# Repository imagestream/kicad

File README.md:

# kicad
Kicad designs and libraries

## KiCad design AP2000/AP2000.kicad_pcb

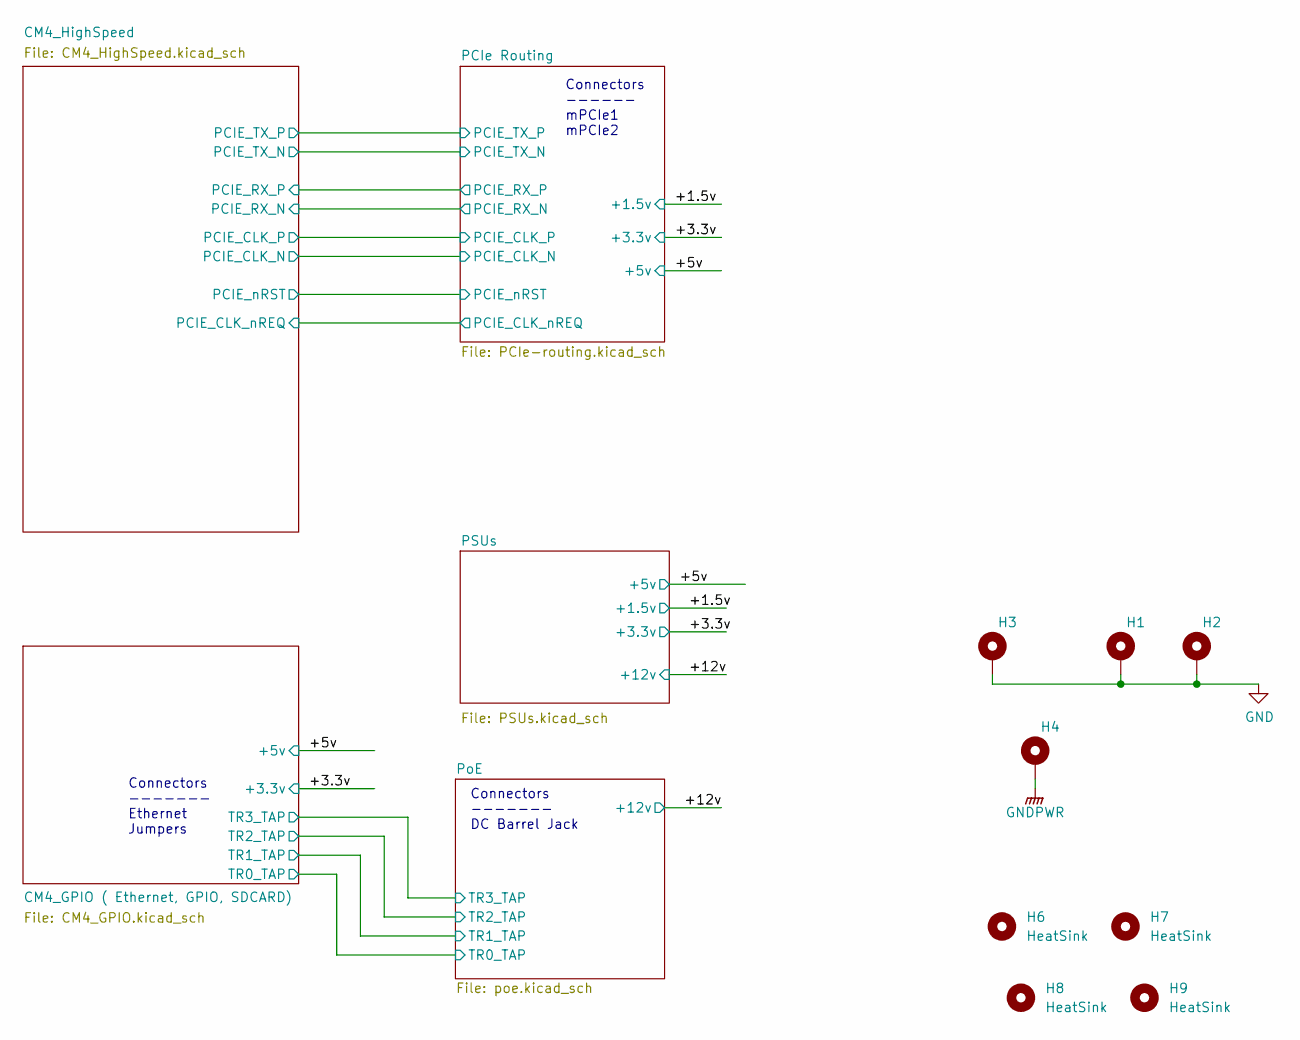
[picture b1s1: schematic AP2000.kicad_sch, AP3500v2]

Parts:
H1: HeatSink; MountingHole_3.7mm_Pad_TopBottom
H2, H3, H4: Mounting Hole; MountingHole_3.7mm_Pad_TopBottom
H6, H7, H8, H9: HeatSink; CM4_Mounting_Hole

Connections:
GND: H1.1, H2.1, H3.1; also elsewhere on the board
GNDPWR: H4.1; also elsewhere on the board

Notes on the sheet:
Connectors ------- Ethernet Jumpers
Connectors ------- DC Barrel Jack
Connectors ------ mPCIe1 mPCIe2

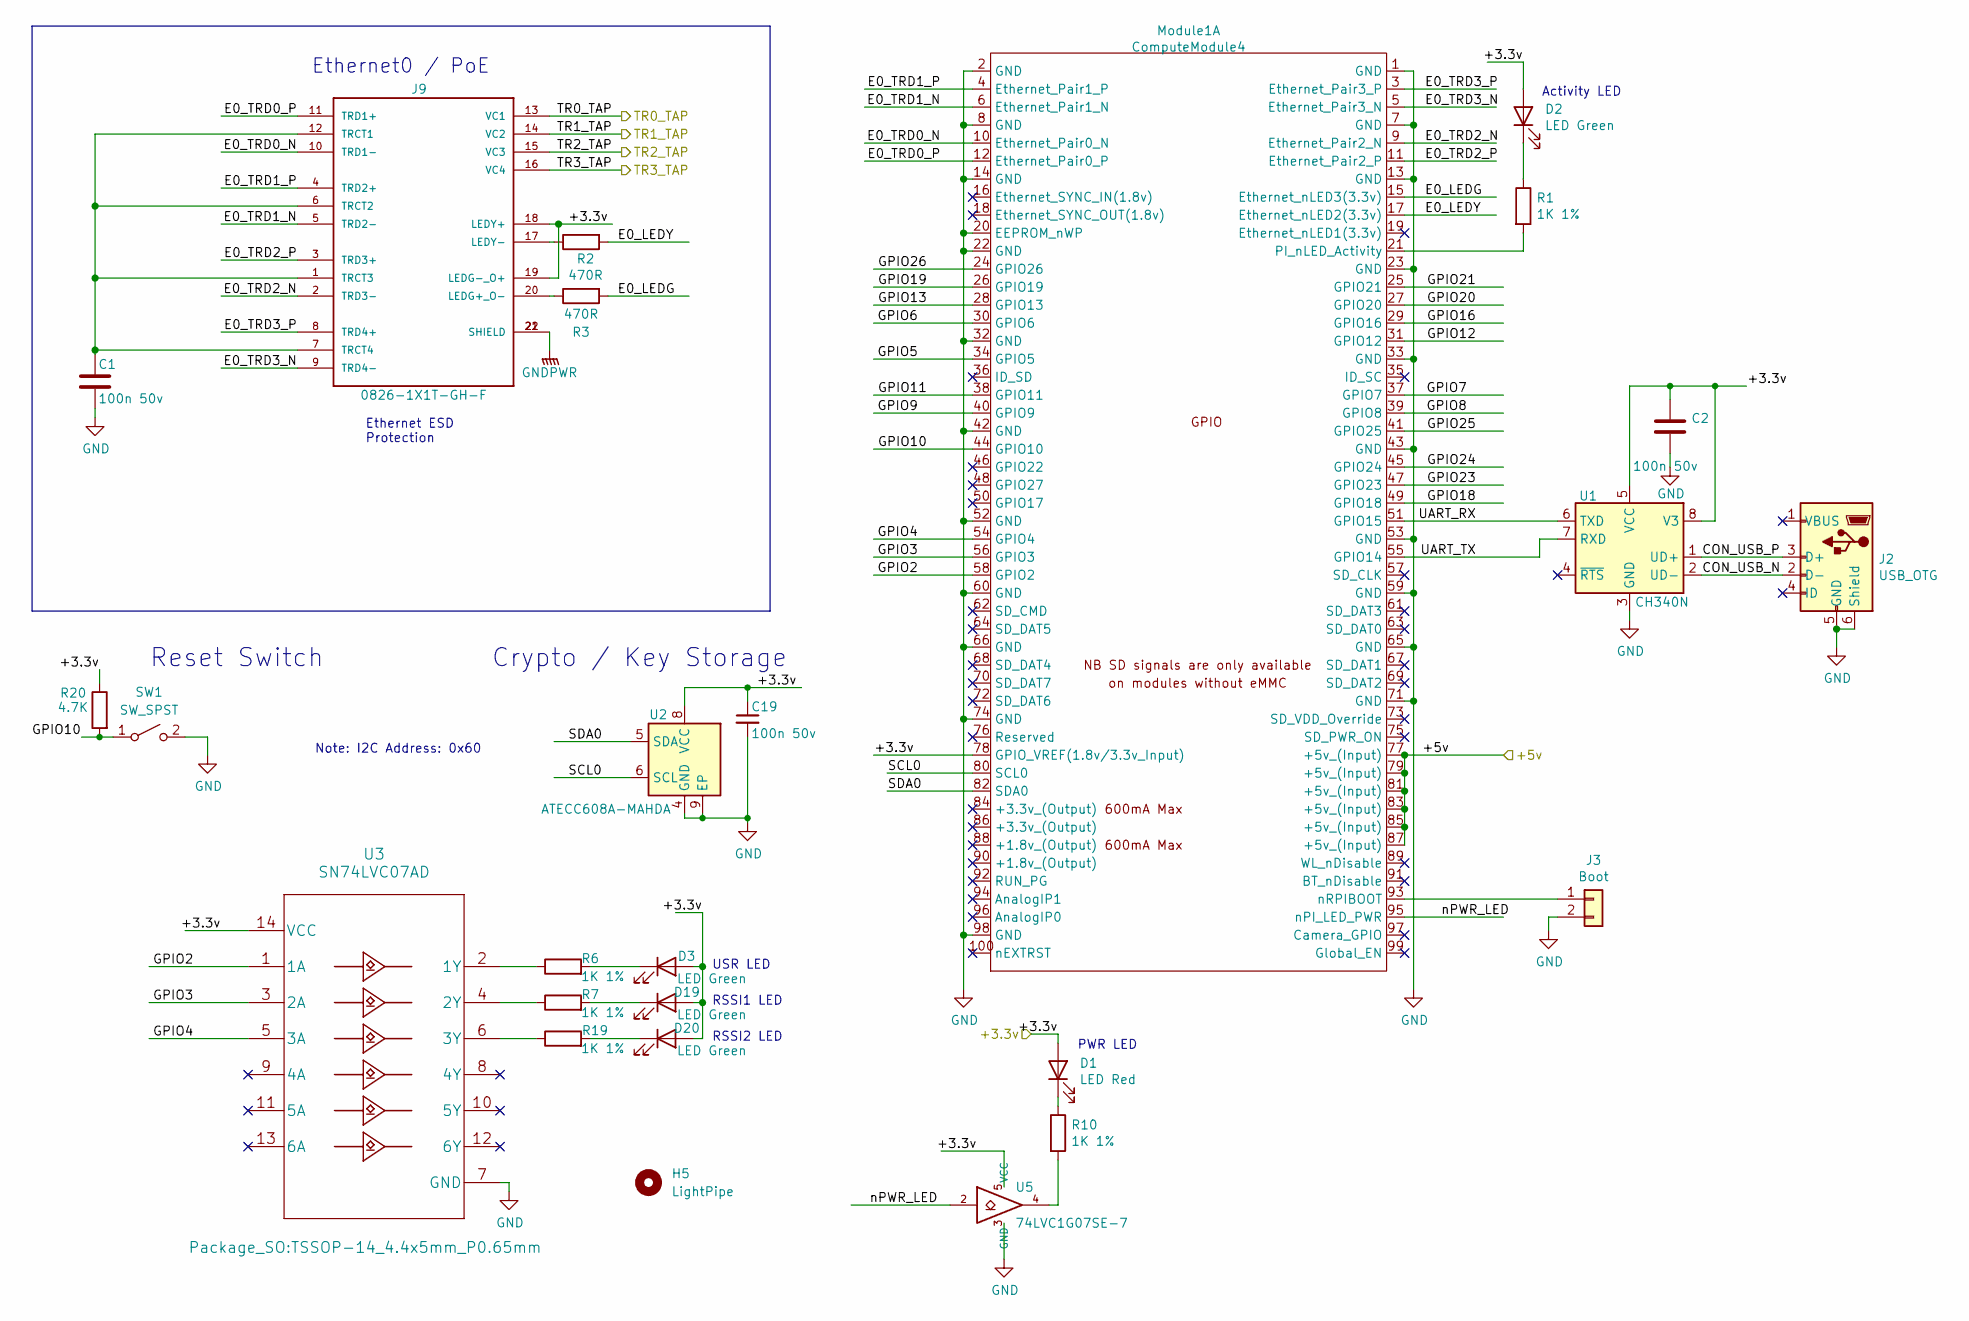
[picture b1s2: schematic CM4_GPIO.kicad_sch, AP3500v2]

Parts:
C1, C2: 100n 50v; C_0603_1608Metric; Part Description 100nF 10% or 20% 50V Ceramic Capacitor 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; LCSC C14663
C19: 100n 50v; C_0603_1608Metric; PartsBoxID 0603-100nF-X7R-50V; LCSC C14663
D1: LED Red; LED_0603_1608Metric; Part Description Red 620nm LED Indication - Discrete 2.2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; LCSC C2286
D2, D3, D19, D20: LED Green; LED_0603_1608Metric; Part Description Green 572nm LED Indication - Discrete 2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; LCSC C72043
H5: LightPipe; VCC_LightPipe_7511A62
J2: USB_OTG; AMPHENOL_10118194-0001LF; Part Description USB - micro B USB 2.0 Receptacle Connec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; LCSC C132563
J3: Boot; PinHeader_1x02_P2.54mm_Vertical; Part Description PinHeader_2x07_P2.54mm_Vertical
J9: 0826-1X1T-GH-F; BEL_0826-1X1T-GH-F; PartsBoxID 0826-1X1T-GH-F
Module1: ComputeModule4; Raspberry-Pi-4-Compute-Module; Part Description 100 Position Connector Receptacle, Cent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
R1, R6, R7, R10, R19: 1K 1%; R_0603_1608Metric; Part Description Resistor 1K M1005 1% 63mW; LCSC C21190
R2, R3: 470R; R_0603_1608Metric; Part Description Resistor 470R M1005 1% 63mW; LCSC C23179
R20: 4.7K; R_0603_1608Metric; PartsBoxID 0603-4.7K-1%; LCSC C23162
SW1: SW_SPST; SWITCH TACTILE SPST-NO 0.05A 12V; PartsBox PTS645VK582LFS
U1: CH340N; SOP-8_5.28x5.23mm_P1.27mm
U2: ATECC608A-MAHDA; DFN-8-1EP_3x2mm_P0.5mm_EP1.3x1.5mm; PartsBoxID ATECC608A-MAHDA-T
U3: SN74LVC07AD; TSSOP-14_4.4x5mm_P0.65mm; PartsBoxID SN74LVC07AD; LCSC C7809
U5: 74LVC1G07SE-7; SOT-23-5; Part Description Buffer, Non-Inverting 1 Element 1 Bit p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; LCSC C7829

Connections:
/+3.3v: C2.1, C19.1, D1.2 (A), D2.2 (A), D3.2 (A), D19.2 (A), D20.2 (A), J9.18 (LEDY+), J9.19 (LEDG-_O+), Module1.78 (GPIO_VREF(1.8v/3.3v_Input)), R20.1, U1.5 (VCC), U1.8 (V3), U2.8 (VCC), U3.14 (VCC), U5.5 (VCC); also elsewhere on the board
/+5v: Module1.77 (+5v_(Input)), Module1.79 (+5v_(Input)), Module1.81 (+5v_(Input)), Module1.83 (+5v_(Input)), Module1.85 (+5v_(Input)), Module1.87 (+5v_(Input)); also elsewhere on the board
/CM4_GPIO ( Ethernet, GPIO, SDCARD)/CON_USB_N: J2.2 (D-), U1.2 (UD-)
/CM4_GPIO ( Ethernet, GPIO, SDCARD)/CON_USB_P: J2.3 (D+), U1.1 (UD+)
/CM4_GPIO ( Ethernet, GPIO, SDCARD)/E0_LEDG: Module1.15 (Ethernet_nLED3(3.3v)), R3.2
/CM4_GPIO ( Ethernet, GPIO, SDCARD)/E0_LEDY: Module1.17 (Ethernet_nLED2(3.3v)), R2.2
/CM4_GPIO ( Ethernet, GPIO, SDCARD)/E0_TRD0_N: J9.10 (TRD1-), Module1.10 (Ethernet_Pair0_N)
/CM4_GPIO ( Ethernet, GPIO, SDCARD)/E0_TRD0_P: J9.11 (TRD1+), Module1.12 (Ethernet_Pair0_P)
/CM4_GPIO ( Ethernet, GPIO, SDCARD)/E0_TRD1_N: J9.5 (TRD2-), Module1.6 (Ethernet_Pair1_N)
/CM4_GPIO ( Ethernet, GPIO, SDCARD)/E0_TRD1_P: J9.4 (TRD2+), Module1.4 (Ethernet_Pair1_P)
/CM4_GPIO ( Ethernet, GPIO, SDCARD)/E0_TRD2_N: J9.2 (TRD3-), Module1.9 (Ethernet_Pair2_N)
/CM4_GPIO ( Ethernet, GPIO, SDCARD)/E0_TRD2_P: J9.3 (TRD3+), Module1.11 (Ethernet_Pair2_P)
/CM4_GPIO ( Ethernet, GPIO, SDCARD)/E0_TRD3_N: J9.9 (TRD4-), Module1.5 (Ethernet_Pair3_N)
/CM4_GPIO ( Ethernet, GPIO, SDCARD)/E0_TRD3_P: J9.8 (TRD4+), Module1.3 (Ethernet_Pair3_P)
/CM4_GPIO ( Ethernet, GPIO, SDCARD)/GPIO2: Module1.58 (GPIO2), U3.1 (1A)
/CM4_GPIO ( Ethernet, GPIO, SDCARD)/GPIO3: Module1.56 (GPIO3), U3.3 (2A)
/CM4_GPIO ( Ethernet, GPIO, SDCARD)/GPIO4: Module1.54 (GPIO4), U3.5 (3A)
/CM4_GPIO ( Ethernet, GPIO, SDCARD)/GPIO5: Module1.34 (GPIO5)
/CM4_GPIO ( Ethernet, GPIO, SDCARD)/GPIO6: Module1.30 (GPIO6)
/CM4_GPIO ( Ethernet, GPIO, SDCARD)/GPIO7: Module1.37 (GPIO7)
/CM4_GPIO ( Ethernet, GPIO, SDCARD)/GPIO8: Module1.39 (GPIO8)
/CM4_GPIO ( Ethernet, GPIO, SDCARD)/GPIO9: Module1.40 (GPIO9)
/CM4_GPIO ( Ethernet, GPIO, SDCARD)/GPIO10: Module1.44 (GPIO10), R20.2, SW1.1 (A)
/CM4_GPIO ( Ethernet, GPIO, SDCARD)/GPIO11: Module1.38 (GPIO11)
/CM4_GPIO ( Ethernet, GPIO, SDCARD)/GPIO12: Module1.31 (GPIO12)
/CM4_GPIO ( Ethernet, GPIO, SDCARD)/GPIO13: Module1.28 (GPIO13)
/CM4_GPIO ( Ethernet, GPIO, SDCARD)/GPIO16: Module1.29 (GPIO16)
/CM4_GPIO ( Ethernet, GPIO, SDCARD)/GPIO18: Module1.49 (GPIO18)
/CM4_GPIO ( Ethernet, GPIO, SDCARD)/GPIO19: Module1.26 (GPIO19)
/CM4_GPIO ( Ethernet, GPIO, SDCARD)/GPIO20: Module1.27 (GPIO20)
/CM4_GPIO ( Ethernet, GPIO, SDCARD)/GPIO21: Module1.25 (GPIO21)
/CM4_GPIO ( Ethernet, GPIO, SDCARD)/GPIO23: Module1.47 (GPIO23)
/CM4_GPIO ( Ethernet, GPIO, SDCARD)/GPIO24: Module1.45 (GPIO24)
/CM4_GPIO ( Ethernet, GPIO, SDCARD)/GPIO25: Module1.41 (GPIO25)
/CM4_GPIO ( Ethernet, GPIO, SDCARD)/GPIO26: Module1.24 (GPIO26)
/CM4_GPIO ( Ethernet, GPIO, SDCARD)/SCL0: Module1.80 (SCL0), U2.6 (SCL)
/CM4_GPIO ( Ethernet, GPIO, SDCARD)/SDA0: Module1.82 (SDA0), U2.5 (SDA)
/CM4_GPIO ( Ethernet, GPIO, SDCARD)/TR0_TAP: J9.13 (VC1); also elsewhere on the board
/CM4_GPIO ( Ethernet, GPIO, SDCARD)/TR1_TAP: J9.14 (VC2); also elsewhere on the board
/CM4_GPIO ( Ethernet, GPIO, SDCARD)/TR2_TAP: J9.15 (VC3); also elsewhere on the board
/CM4_GPIO ( Ethernet, GPIO, SDCARD)/TR3_TAP: J9.16 (VC4); also elsewhere on the board
/CM4_GPIO ( Ethernet, GPIO, SDCARD)/UART_RX: Module1.51 (GPIO15), U1.6 (TXD)
/CM4_GPIO ( Ethernet, GPIO, SDCARD)/UART_TX: Module1.55 (GPIO14), U1.7 (RXD)
/CM4_GPIO ( Ethernet, GPIO, SDCARD)/nPWR_LED: Module1.95 (nPI_LED_PWR), U5.2
GND: C1.2, C2.2, C19.2, J2.5 (GND), J2.6 (Shield), J3.2, Module1.1 (GND), Module1.2 (GND), Module1.7 (GND), Module1.8 (GND), Module1.13 (GND), Module1.14 (GND), Module1.20 (EEPROM_nWP), Module1.22 (GND), Module1.23 (GND), Module1.32 (GND), Module1.33 (GND), Module1.42 (GND), Module1.43 (GND), Module1.52 (GND), Module1.53 (GND), Module1.59 (GND), Module1.60 (GND), Module1.65 (GND), Module1.66 (GND), Module1.71 (GND), Module1.74 (GND), Module1.98 (GND), SW1.2 (B), U1.3 (GND), U2.4 (GND), U2.9 (EP), U3.7 (GND), U5.3 (GND); also elsewhere on the board
GNDPWR: J9.21 (SHIELD), J9.22 (SHIELD); also elsewhere on the board
unnamed: C1.1, J9.1 (TRCT3), J9.6 (TRCT2), J9.7 (TRCT4), J9.12 (TRCT1)
unnamed: D1.1 (K), R10.1
unnamed: D2.1 (K), R1.1
unnamed: D3.1 (K), R6.2
unnamed: D19.1 (K), R7.2
unnamed: D20.1 (K), R19.2
unnamed: J3.1, Module1.93 (nRPIBOOT)
unnamed: J9.17 (LEDY-), R2.1
unnamed: J9.20 (LEDG+_O-), R3.1
unnamed: Module1.21 (PI_nLED_Activity), R1.2
unnamed: R6.1, U3.2 (1Y)
unnamed: R7.1, U3.4 (2Y)
unnamed: R10.2, U5.4
unnamed: R19.1, U3.6 (3Y)

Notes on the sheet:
Ethernet0 / PoE
Reset Switch
Ethernet ESD Protection
Note: I2C Address: 0x60
USR LED
RSSI1 LED
RSSI2 LED
Crypto / Key Storage
PWR LED
Activity LED

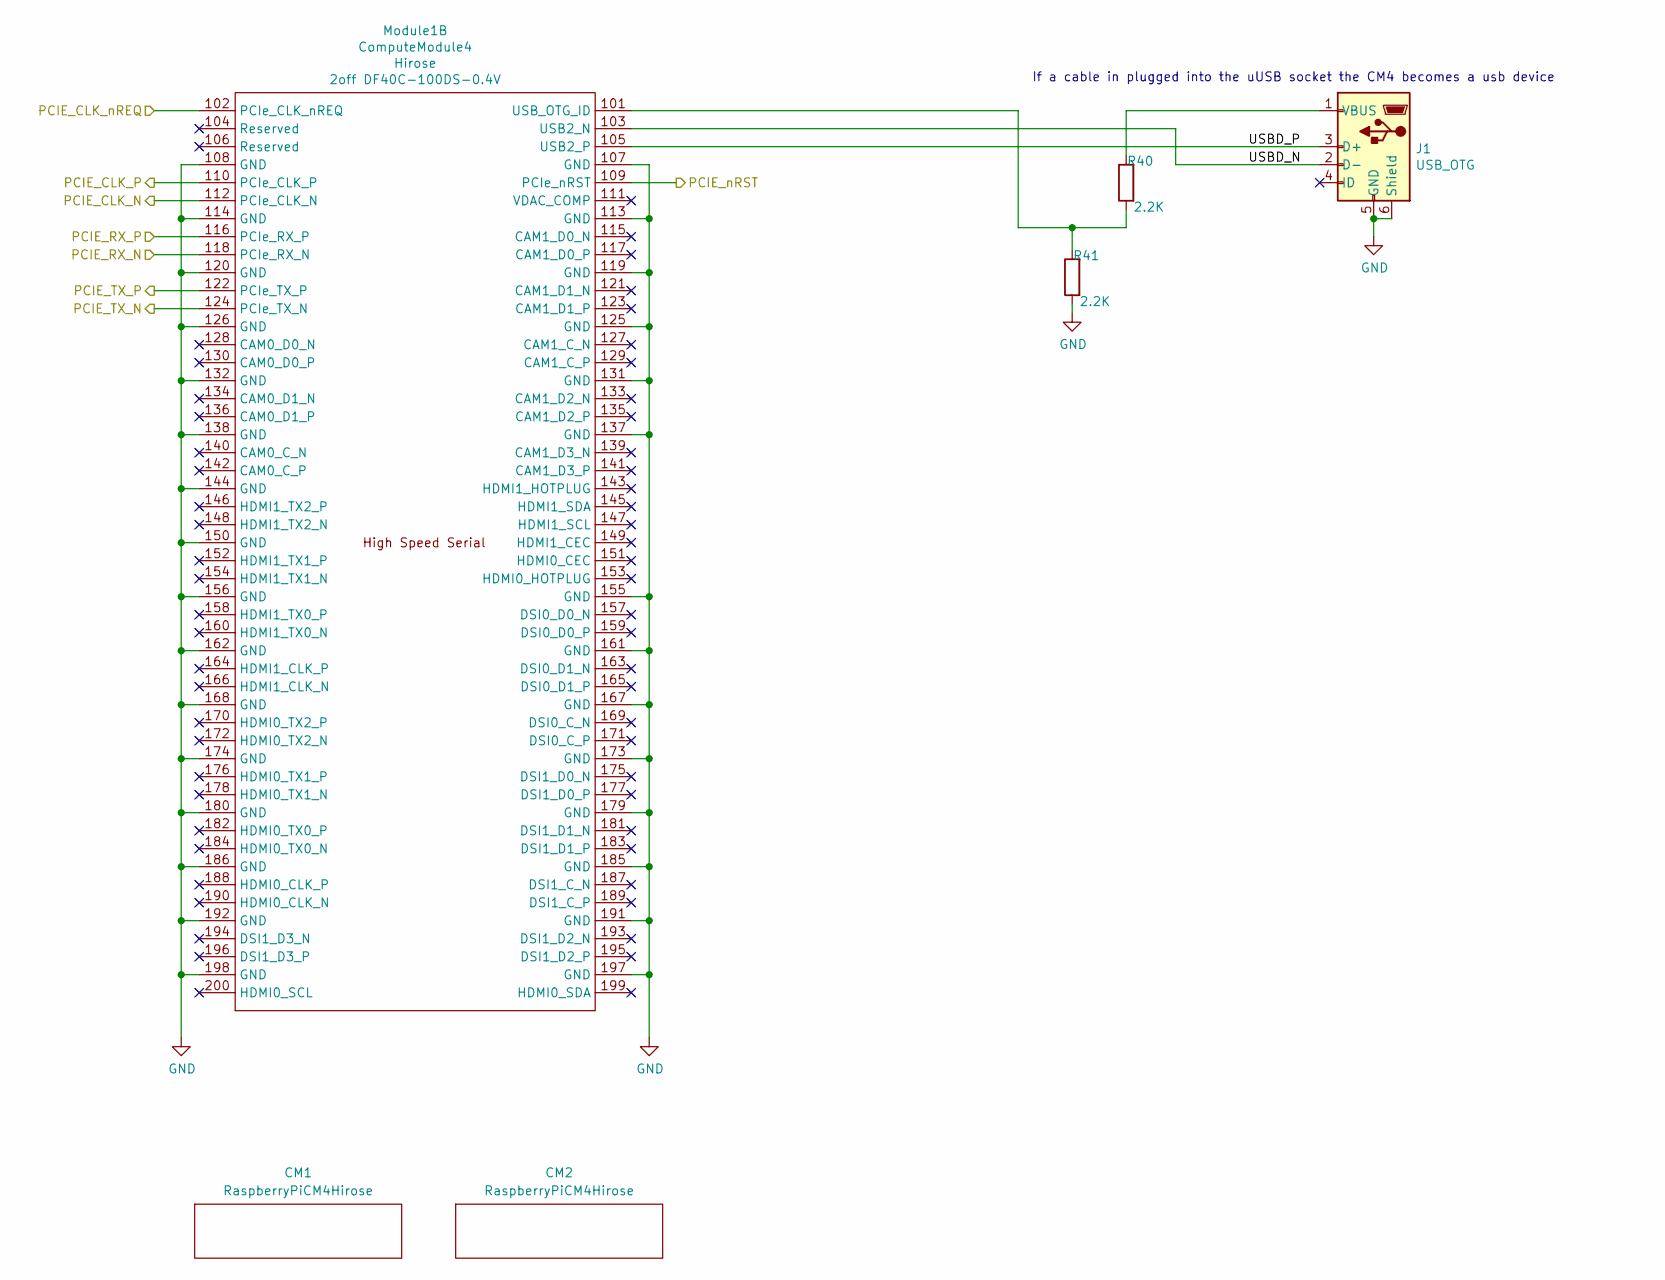
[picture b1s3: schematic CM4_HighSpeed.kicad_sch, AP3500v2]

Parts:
CM1, CM2: RaspberryPiCM4Hirose; Hirose-DF40C-100DS-0.4V; LCSC C424649
J1: USB_OTG; AMPHENOL_10118194-0001LF; Part Description USB - micro B USB 2.0 Receptacle Connec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; LCSC C132563
Module1: ComputeModule4; Raspberry-Pi-4-Compute-Module; Part Description 100 Position Connector Receptacle, Cent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
R40, R41: 2.2K; R_0603_1608Metric; PartsBoxID 0603-2.2K-1%; LCSC C4190

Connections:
/CM4_HighSpeed/PCIE_CLK_N: Module1.112 (PCIe_CLK_N); also elsewhere on the board
/CM4_HighSpeed/PCIE_CLK_P: Module1.110 (PCIe_CLK_P); also elsewhere on the board
/CM4_HighSpeed/PCIE_CLK_nREQ: Module1.102 (PCIe_CLK_nREQ); also elsewhere on the board
/CM4_HighSpeed/PCIE_RX_N: Module1.118 (PCIe_RX_N); also elsewhere on the board
/CM4_HighSpeed/PCIE_RX_P: Module1.116 (PCIe_RX_P); also elsewhere on the board
/CM4_HighSpeed/PCIE_TX_N: Module1.124 (PCIe_TX_N); also elsewhere on the board
/CM4_HighSpeed/PCIE_TX_P: Module1.122 (PCIe_TX_P); also elsewhere on the board
/CM4_HighSpeed/PCIE_nRST: Module1.109 (PCIe_nRST); also elsewhere on the board
/CM4_HighSpeed/USBD_N: J1.2 (D-), Module1.103 (USB2_N)
/CM4_HighSpeed/USBD_P: J1.3 (D+), Module1.105 (USB2_P)
GND: J1.5 (GND), J1.6 (Shield), Module1.107 (GND), Module1.108 (GND), Module1.113 (GND), Module1.114 (GND), Module1.119 (GND), Module1.120 (GND), Module1.125 (GND), Module1.126 (GND), Module1.131 (GND), Module1.132 (GND), Module1.137 (GND), Module1.138 (GND), Module1.144 (GND), Module1.150 (GND), Module1.155 (GND), Module1.156 (GND), Module1.161 (GND), Module1.162 (GND), Module1.167 (GND), Module1.168 (GND), Module1.173 (GND), Module1.174 (GND), Module1.179 (GND), Module1.180 (GND), Module1.185 (GND), Module1.186 (GND), Module1.191 (GND), Module1.192 (GND), Module1.197 (GND), Module1.198 (GND), R41.2; also elsewhere on the board
unnamed: J1.1 (VBUS), R40.1
unnamed: Module1.101 (USB_OTG_ID), R40.2, R41.1

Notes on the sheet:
If a cable in plugged into the uUSB socket the CM4 becomes a usb device

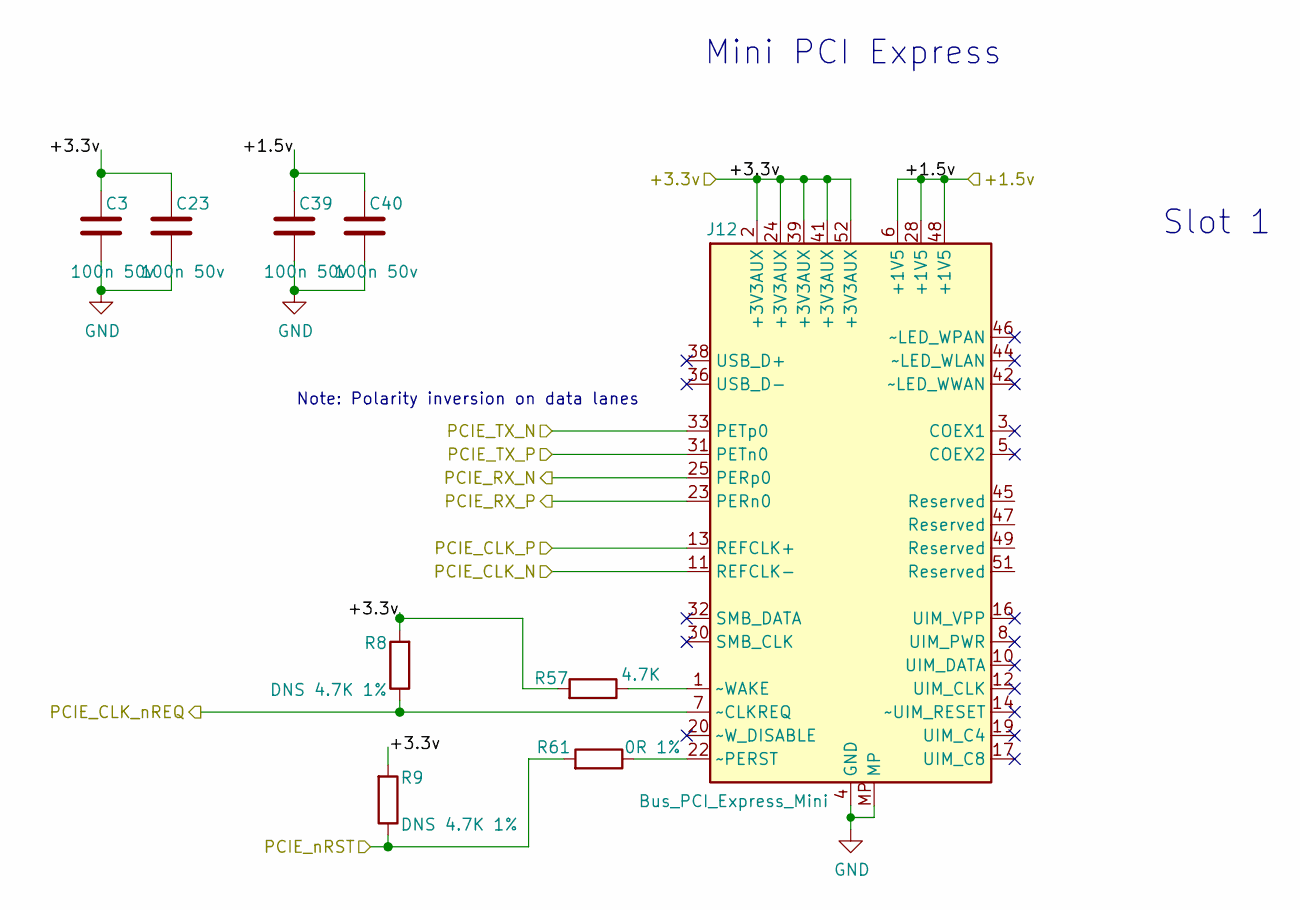
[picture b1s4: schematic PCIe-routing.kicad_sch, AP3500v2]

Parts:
C3, C23, C39, C40: 100n 50v; C_0603_1608Metric; Part Description .1uF 10% or 20% 25V Ceramic Capacitor X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; LCSC C14663
J12: Bus_PCI_Express_Mini; BUS_PCI_Express_Mini_Full; PartsBoxID 1775838-2; LCSC C404121
R8, R9: DNS 4.7K 1%; R_0603_1608Metric; PartsBoxID 0603-4.7K-1%
R57: 4.7K; R_0603_1608Metric; PartsBoxID 0603-4.7K-1%; LCSC C23162
R61: 0R 1%; R_0603_1608Metric; LCSC C21189

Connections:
/+1.5v: C39.1, C40.1, J12.6 (+1V5), J12.28 (+1V5), J12.48 (+1V5); also elsewhere on the board
/+3.3v: C3.1, C23.1, J12.2 (+3V3AUX), J12.24 (+3V3AUX), J12.39 (+3V3AUX), J12.41 (+3V3AUX), J12.52 (+3V3AUX), R8.2, R9.2, R57.2; also elsewhere on the board
/CM4_HighSpeed/PCIE_CLK_N: J12.11 (REFCLK-); also elsewhere on the board
/CM4_HighSpeed/PCIE_CLK_P: J12.13 (REFCLK+); also elsewhere on the board
/CM4_HighSpeed/PCIE_CLK_nREQ: J12.7 (~CLKREQ), R8.1; also elsewhere on the board
/CM4_HighSpeed/PCIE_RX_N: J12.25 (PERp0); also elsewhere on the board
/CM4_HighSpeed/PCIE_RX_P: J12.23 (PERn0); also elsewhere on the board
/CM4_HighSpeed/PCIE_TX_N: J12.33 (PETp0); also elsewhere on the board
/CM4_HighSpeed/PCIE_TX_P: J12.31 (PETn0); also elsewhere on the board
/CM4_HighSpeed/PCIE_nRST: R9.1, R61.2; also elsewhere on the board
GND: C3.2, C23.2, C39.2, C40.2, J12.4 (GND), J12.9 (GND), J12.15 (GND), J12.18 (GND), J12.21 (GND), J12.26 (GND), J12.27 (GND), J12.29 (GND), J12.34 (GND), J12.35 (GND), J12.37 (GND), J12.40 (GND), J12.43 (GND), J12.50 (GND), J12.MP; also elsewhere on the board
unnamed: J12.1 (~WAKE), R57.1
unnamed: J12.22 (~PERST), R61.1

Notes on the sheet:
Note: Polarity inversion on data lanes
Mini PCI Express
Slot 1

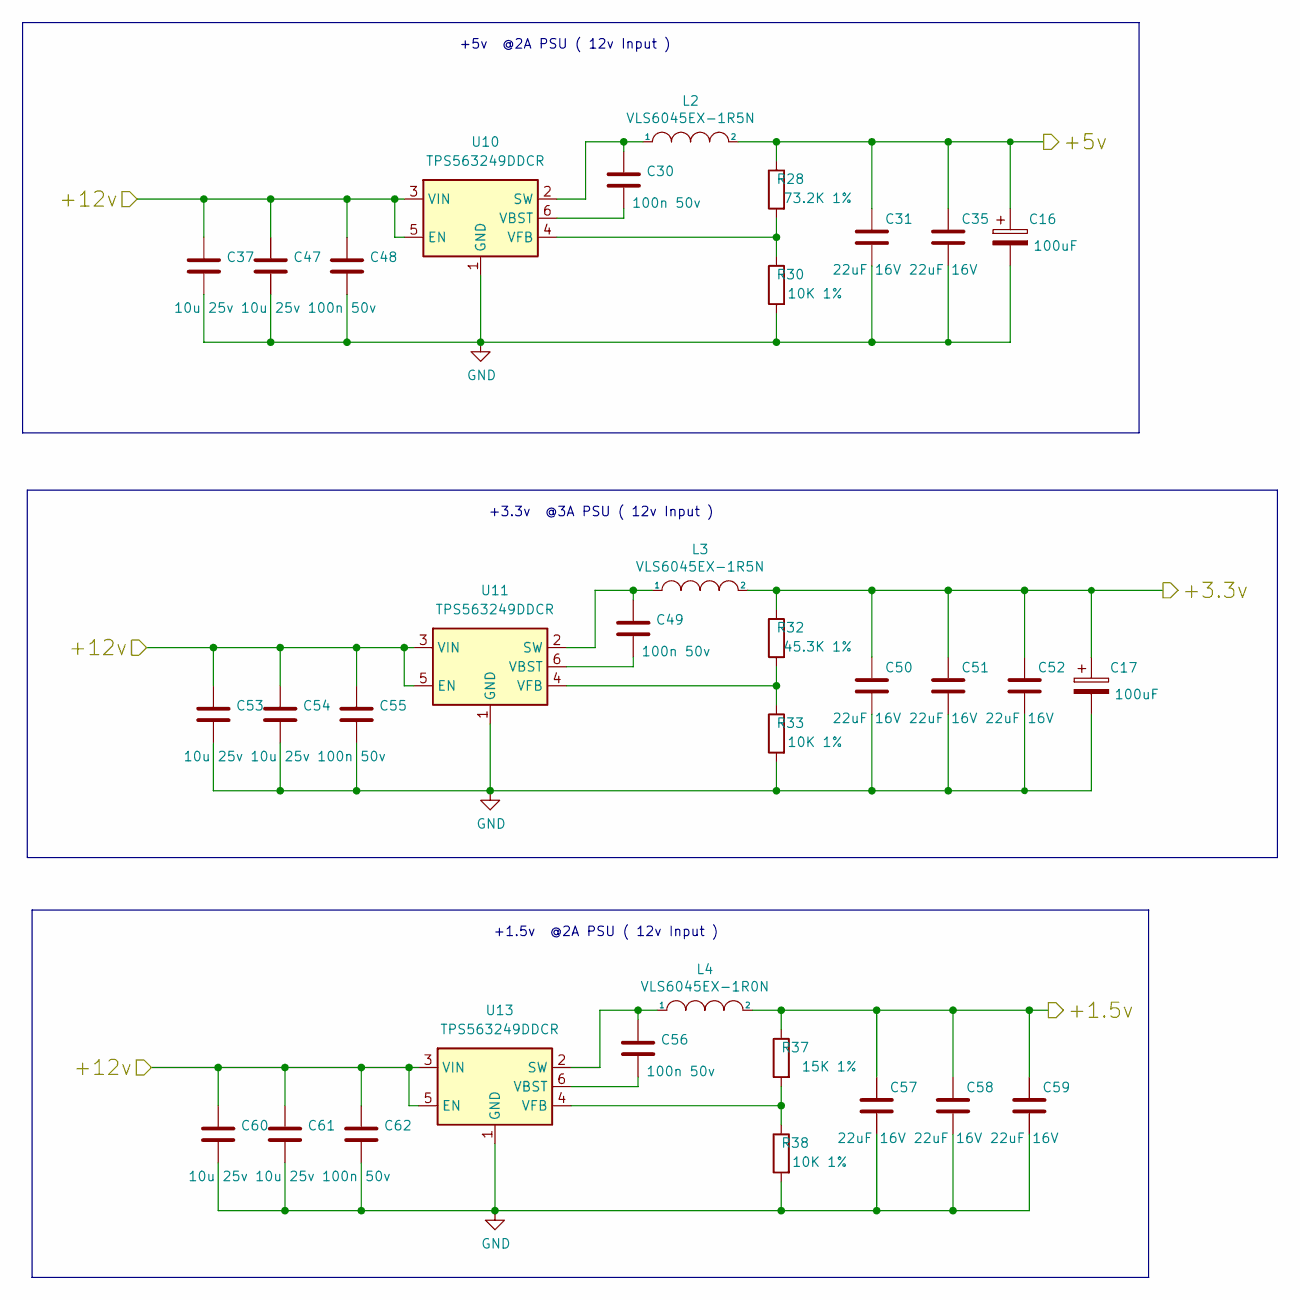
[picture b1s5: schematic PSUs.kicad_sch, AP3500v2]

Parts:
C16, C17: 100uF; CP_EIA-3528-21_Kemet-B_Pad1.50x2.35mm_HandSolder; Part Description Capacitor, SP-Cap, 100u, 6.3V, 15mR ESR; LCSC C16133
C30, C49, C56: 100n 50v; C_0603_1608Metric; LCSC C14663
C31, C35, C50, C51, C52, C57, C58, C59: 22uF 16V; C_1206_3216Metric; Part Description GCM32ER71C226KE19L; LCSC C90146
C37, C47, C53, C54, C60, C61: 10u 25v; C_0805_2012Metric; Part Description 10uF 10% or 20% 10V Ceramic Capacitor X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; LCSC C15850
C48, C55, C62: 100n 50v; C_0603_1608Metric; Part Description 100nF 10% or 20% 50V Ceramic Capacitor 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; LCSC C14663
L2, L3: VLS6045EX-1R5N; L_TDK_VLS6045; PartsBoxID VLS6045EX-1R5N
L4: VLS6045EX-1R0N; L_TDK_VLS6045; PartsBoxID VLS6045EX-1R0N
R28: 73.2K 1%; R_0603_1608Metric; LCSC C14890
R30, R33, R38: 10K 1%; R_0603_1608Metric; LCSC C25804
R32: 45.3K 1%; R_0603_1608Metric; LCSC C23058
R37: 15K 1%; R_0603_1608Metric; LCSC C22809
U10, U11, U13: TPS563249DDCR; SOT-23-6; PartsBoxID TPS563249DDCR

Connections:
/+1.5v: C57.1, C58.1, C59.1, L4.2, R37.1; also elsewhere on the board
/+3.3v: C17.1, C50.1, C51.1, C52.1, L3.2, R32.1; also elsewhere on the board
/+5v: C16.1, C31.1, C35.1, L2.2, R28.1; also elsewhere on the board
/+12v: C37.1, C47.1, C48.1, C53.1, C54.1, C55.1, C60.1, C61.1, C62.1, U10.3 (VIN), U10.5 (EN), U11.3 (VIN), U11.5 (EN), U13.3 (VIN), U13.5 (EN); also elsewhere on the board
GND: C16.2, C17.2, C31.2, C35.2, C37.2, C47.2, C48.2, C50.2, C51.2, C52.2, C53.2, C54.2, C55.2, C57.2, C58.2, C59.2, C60.2, C61.2, C62.2, R30.2, R33.2, R38.2, U10.1 (GND), U11.1 (GND), U13.1 (GND); also elsewhere on the board
unnamed: C30.1, L2.1, U10.2 (SW)
unnamed: C30.2, U10.6 (VBST)
unnamed: C49.1, L3.1, U11.2 (SW)
unnamed: C49.2, U11.6 (VBST)
unnamed: C56.1, L4.1, U13.2 (SW)
unnamed: C56.2, U13.6 (VBST)
unnamed: R28.2, R30.1, U10.4 (VFB)
unnamed: R32.2, R33.1, U11.4 (VFB)
unnamed: R37.2, R38.1, U13.4 (VFB)

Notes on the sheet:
+5v @2A PSU ( 12v Input )
+3.3v @3A PSU ( 12v Input )
+1.5v @2A PSU ( 12v Input )

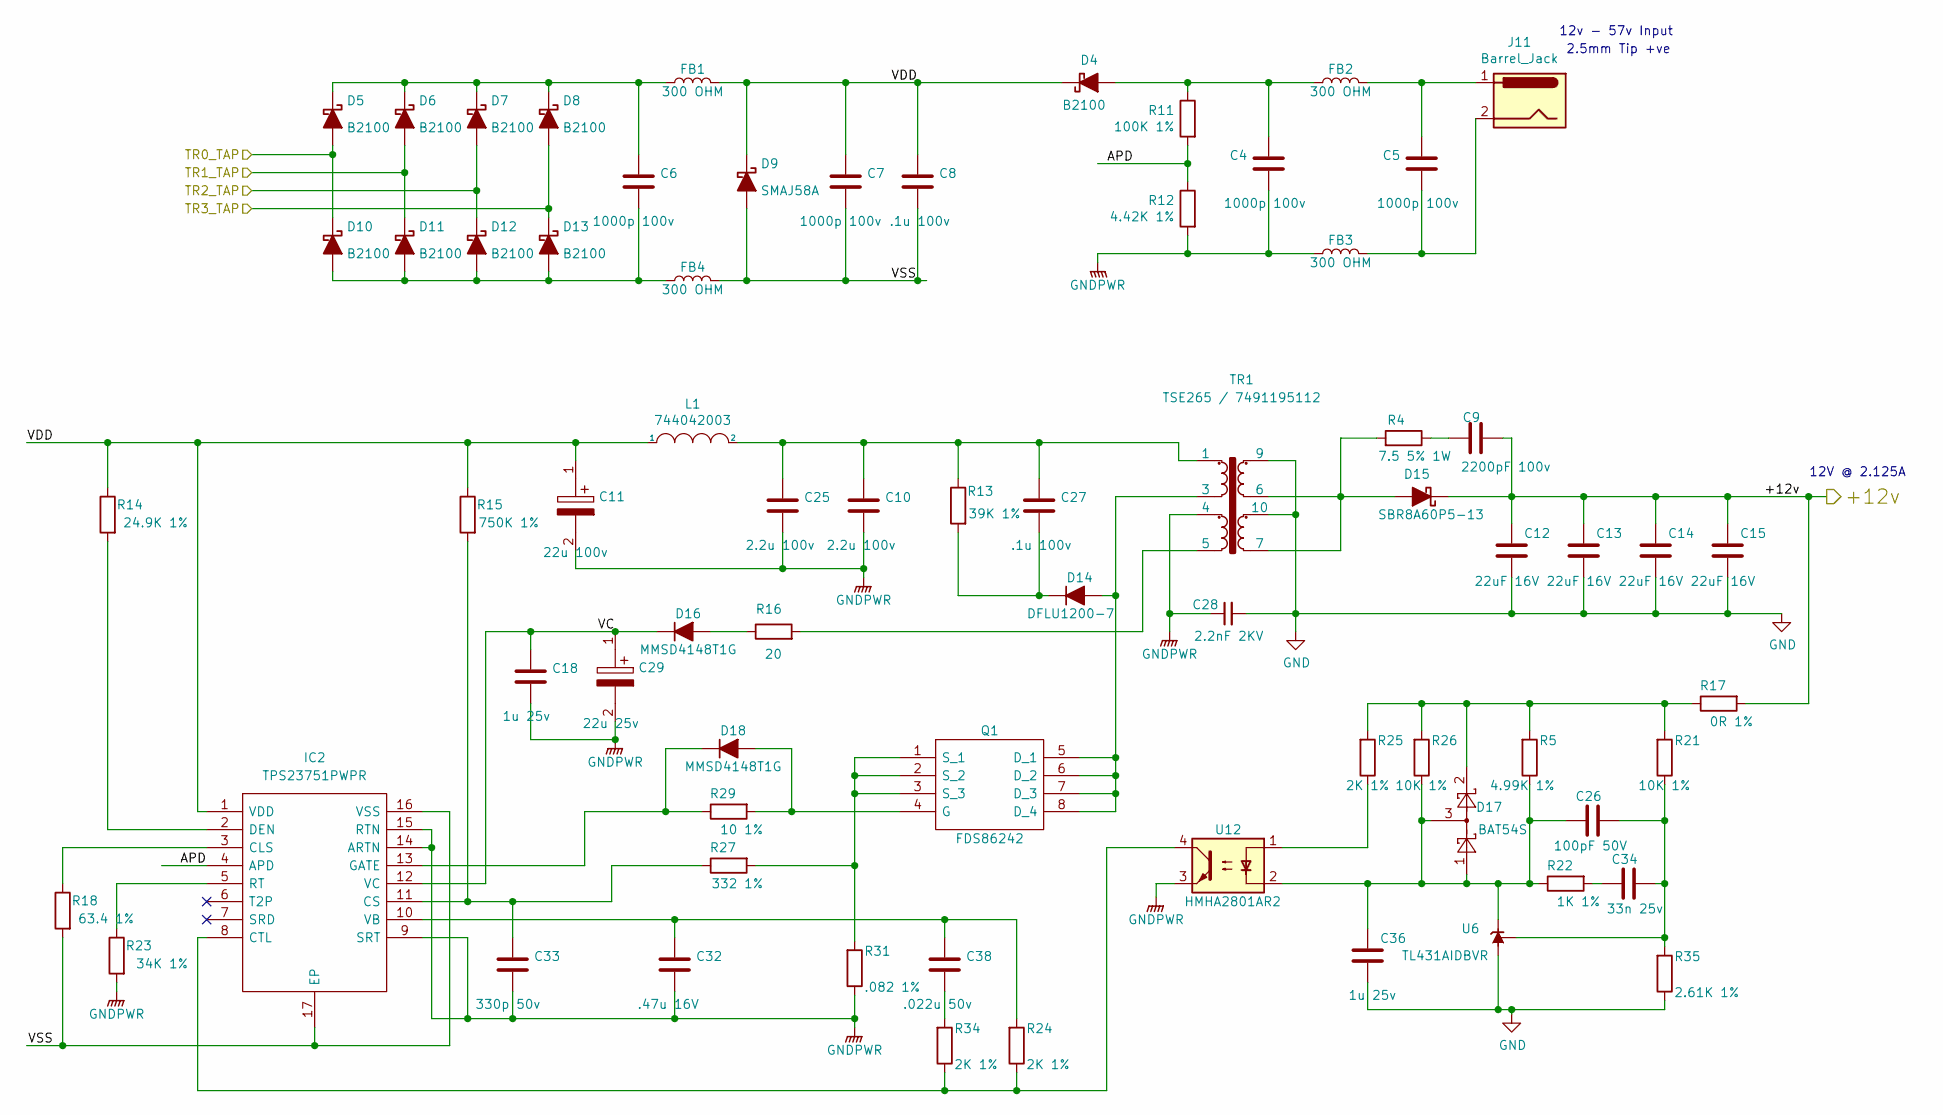
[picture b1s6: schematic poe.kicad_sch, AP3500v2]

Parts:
C4, C5, C6, C7: 1000p 100v; C_0805_2012Metric; Part Description 1000pF 10% or 20% 100V Ceramic Capacito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; LCSC C15177
C8, C27: .1u 100v; C_0603_1608Metric; Part Description .1uF 10% or 20% 100V Ceramic Capacitor 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; LCSC C15725
C9: 2200pF 100v; C_0603_1608Metric; Part Description 0603-2200pF-X7R-100V; LCSC C22423
C10, C25: 2.2u 100v; C_1210_3225Metric; LCSC C55151
C11: 22u 100v; CP_Elec_8x10.5; PartsBoxID AEC-SMD-8mm-22uF-100VDC-20%; LCSC C249491
C12, C13, C14, C15: 22uF 16V; C_1206_3216Metric; Part Description GCM32ER71C226KE19L; LCSC C90146
C18: 1u 25v; C_0805_2012Metric; Part Description C2012X5R1E105K; LCSC C89190
C26: 100pF 50V; C_0603_1608Metric; LCSC C14858
C28: 2.2nF 2KV; C_1210_3225Metric; PartsBoxID 1210-2.2nF-X7R-2KV; LCSC C173219
C29: 22u 25v; CP_Elec_5x5.4; PartsBoxID EEEFK1E220R; LCSC C239255
C32: .47u 16V; C_0603_1608Metric; Part Description .47uF 10% or 20% 16V Ceramic Capacitor 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; LCSC C1623
C33: 330p 50v; C_0603_1608Metric; Part Description 330pF 10% or 20% 50V Ceramic Capacitor 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; LCSC C1664
C34: 33n 25v; C_0603_1608Metric; LCSC C21117
C36: 1u 25v; C_0805_2012Metric; LCSC C89190
C38: .022u 50v; C_0603_1608Metric; Part Description .022uF 10% or 20% 50V Ceramic Capacitor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; LCSC C21122
D4, D5, D6, D7, D8, D10, D11, D12, D13: B2100; D_SMA; PartsBoxID B2100AE-13; LCSC C388246
D9: SMAJ58A; D_SMA; PartsBoxID SMAJ58A; Mouser Part Number 576-SMAJ58A
D14: DFLU1200-7; D_PowerDI-123; PartsBoxID DFLU1200-7
D15: SBR8A60P5-13; D_PowerDI-5; PartsBoxID SBR8A60P5-13
D16, D18: MMSD4148T1G; D_SOD-123; PartsBoxID MMSD4148T1G; LCSC C132796
D17: BAT54S; SOT-23; PartsBoxID BAT54SW-7-F; LCSC C727126
FB1, FB2, FB3, FB4: 300 OHM; L_0805_2012Metric; PartsBoxID 742792641; LCSC C56066
IC2: TPS23751PWPR; HTSSOP-16-1EP_4.4x5mm_P0.65mm_EP3.4x5mm_Mask2.46x2.31mm_The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; Manufacturer_Part_Number TPS23751PWPR; Mouser Part Number 595-TPS23751PWPR
J11: Barrel_Jack; BarrelJack_Horizontal; PartsBoxID BJ-2.5MM
L1: 744042003; WE-TPC_4818_482892-744042003; PartsBoxID 744042003
Q1: FDS86242; SO-8_3.9x4.9mm_P1.27mm; PartsBoxID FDS86242; LCSC C148410
R4: 7.5 5% 1W; R_2512_6332Metric; Part Description Resistor 7.5 2512 5% 1W; LCSC C35217
R5: 4.99K 1%; R_0603_1608Metric; LCSC C23046
R11: 100K 1%; R_0603_1608Metric; Part Description Resistor 100K 0402 1% 63mW; LCSC C25803
R12: 4.42K 1%; R_0603_1608Metric; LCSC C23043
R13: 39K 1%; R_0805_2012Metric; Part Description Resistor 39K 0805 1% 250mW; LCSC C25826
R14: 24.9K 1%; R_0603_1608Metric; Part Description Resistor 24.9K 0603 .1% 63mW; LCSC C25962
R15: 750K 1%; R_0603_1608Metric; Part Description Resistor 750K 0402 1% 63mW; LCSC C23240
R16: 20; R_0805_2012Metric; PartsBoxID CRCW080520R0JNEA; LCSC C17544
R17: 0R 1%; R_0603_1608Metric; Part Description Resistor 49.9 0402 1% 63mW; LCSC C21189
R18: 63.4 1%; R_0603_1608Metric; Part Description Resistor 63.4 0402 1% 100mW; LCSC C23223
R21, R26: 10K 1%; R_0603_1608Metric; Part Description Resistor 10K 0402 1% 63mW; LCSC C25804
R22: 1K 1%; R_0603_1608Metric; LCSC C21190
R23: 34K 1%; R_0603_1608Metric; Part Description Resistor 34K 0402 1% 63mW; LCSC C23008
R24, R25, R34: 2K 1%; R_0603_1608Metric; LCSC C22975
R27: 332 1%; R_0603_1608Metric; Part Description Resistor 332 0402 1% 63mW; LCSC C23007
R29: 10 1%; R_0603_1608Metric; Part Description Resistor 43.2 0402 1% 63mW; LCSC C22859
R31: .082 1%; R_1206_3216Metric; LCSC C247543
R35: 2.61K 1%; R_0603_1608Metric; LCSC C22942
TR1: TSE265 / 7491195112; Transformer_EP13; PartsBoxID 7491195112
U6: TL431AIDBVR; SOT-23; PartsBoxID TL431AIDBVR; LCSC C23892
U12: HMHA2801AR2; SOP-4_4.4x2.6mm_P1.27mm; PartsBoxID HMHA2801AR2; LCSC C258257

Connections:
/+12v: C9.2, C12.1, C13.1, C14.1, C15.1, D15.1 (K), R17.2; also elsewhere on the board
/CM4_GPIO ( Ethernet, GPIO, SDCARD)/TR0_TAP: D5.2 (A), D10.1 (K); also elsewhere on the board
/CM4_GPIO ( Ethernet, GPIO, SDCARD)/TR1_TAP: D6.2 (A), D11.1 (K); also elsewhere on the board
/CM4_GPIO ( Ethernet, GPIO, SDCARD)/TR2_TAP: D7.2 (A), D12.1 (K); also elsewhere on the board
/CM4_GPIO ( Ethernet, GPIO, SDCARD)/TR3_TAP: D8.2 (A), D13.1 (K); also elsewhere on the board
/PoE/APD: IC2.4 (APD), R11.2, R12.1
/PoE/VC: C18.1, C29.1, D16.1 (K), IC2.12 (VC)
/PoE/VDD: C7.1, C8.1, C11.1, D4.1 (K), D9.1 (K), FB1.2, IC2.1 (VDD), L1.1, R14.1, R15.1
/PoE/VSS: C7.2, C8.2, D9.2 (A), FB4.2, IC2.16 (VSS), IC2.17 (EP), R18.2
GND: C12.2, C13.2, C14.2, C15.2, C28.2, C36.2, R35.1, TR1.9, TR1.10, U6.3 (A); also elsewhere on the board
GNDPWR: C4.2, C10.2, C11.2, C18.2, C25.2, C28.1, C29.2, C32.2, C33.2, FB3.2, IC2.9 (SRT), IC2.14 (ARTN), IC2.15 (RTN), R12.2, R23.2, R31.1, TR1.4, U12.3; also elsewhere on the board
unnamed: C4.1, D4.2 (A), FB2.2, R11.1
unnamed: C5.1, FB2.1, J11.1
unnamed: C5.2, FB3.1, J11.2
unnamed: C6.1, D5.1 (K), D6.1 (K), D7.1 (K), D8.1 (K), FB1.1
unnamed: C6.2, D10.2 (A), D11.2 (A), D12.2 (A), D13.2 (A), FB4.1
unnamed: C9.1, R4.1
unnamed: C10.1, C25.1, C27.1, L1.2, R13.1, TR1.1
unnamed: C26.1, C36.1, D17.1, D17.3, R5.1, R22.1, R26.1, U6.1 (K), U12.2
unnamed: C26.2, C34.2, R21.1, R35.2, U6.2 (REF)
unnamed: C27.2, D14.1 (K), R13.2
unnamed: C32.1, C38.1, IC2.10 (VB), R24.2
unnamed: C33.1, IC2.11 (CS), R15.2, R27.1
unnamed: C34.1, R22.2
unnamed: C38.2, R34.2
unnamed: D14.2 (A), Q1.5 (D_1), Q1.6 (D_2), Q1.7 (D_3), Q1.8 (D_4), TR1.3
unnamed: D15.2 (A), R4.2, TR1.6, TR1.7
unnamed: D16.2 (A), R16.1
unnamed: D17.2, R5.2, R17.1, R21.2, R25.2, R26.2
unnamed: D18.1 (K), IC2.13 (GATE), R29.1
unnamed: D18.2 (A), Q1.4 (G), R29.2
unnamed: IC2.2 (DEN), R14.2
unnamed: IC2.3 (CLS), R18.1
unnamed: IC2.5 (RT), R23.1
unnamed: IC2.8 (CTL), R24.1, R34.1, U12.4
unnamed: Q1.1 (S_1), Q1.2 (S_2), Q1.3 (S_3), R27.2, R31.2
unnamed: R16.2, TR1.5
unnamed: R25.1, U12.1

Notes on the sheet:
2.5mm Tip +ve
12v - 57v Input
12V @ 2.125A

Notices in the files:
AP2000/AP2000.kicad_pcb:
Copyright 2021
parts and their libraries:
Copyright 2021 Accelerated Designs. All rights reserved.
